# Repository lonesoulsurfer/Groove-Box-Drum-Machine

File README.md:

# Groove Box Drum Machine
An Arduino Nano based drum machine based on the awesome DrumKid build (https://github.com/mattybrad/drumkid) by Matt Bradshaw.  My version includes 3 X trigger outputs so you can sync with other synths.  I've also designed it so it will fit into any Eurorack and can be powered by either a standard 16 pin Eurorack power input or a 9V JST connector.

You can find a step by step guide on my Instructables page on how to build your own - https://www.instructables.com/Groove-Box-Arduino-Nano-Drum-Machine/

I have also posted a video on my YouTube page - https://youtu.be/VaNvsRpYE2A

The main goal with building this module is to create my own 'simple to build' modular synth. I wanted to keep everything as easy as possble with each module built with the following aims:

 - Can be powered by 9V (and 12V)
 - Easy to build with minimum components
 - Use Arduino to keep it simple (plus it helps to keep the components down and everything in tune)
 - Can fit into any modular synth Eurorck (include the ability to power the module via normal module power sources)
 - Has to sound great!
- Lastly, it should be portable and be powered from a 9V battery

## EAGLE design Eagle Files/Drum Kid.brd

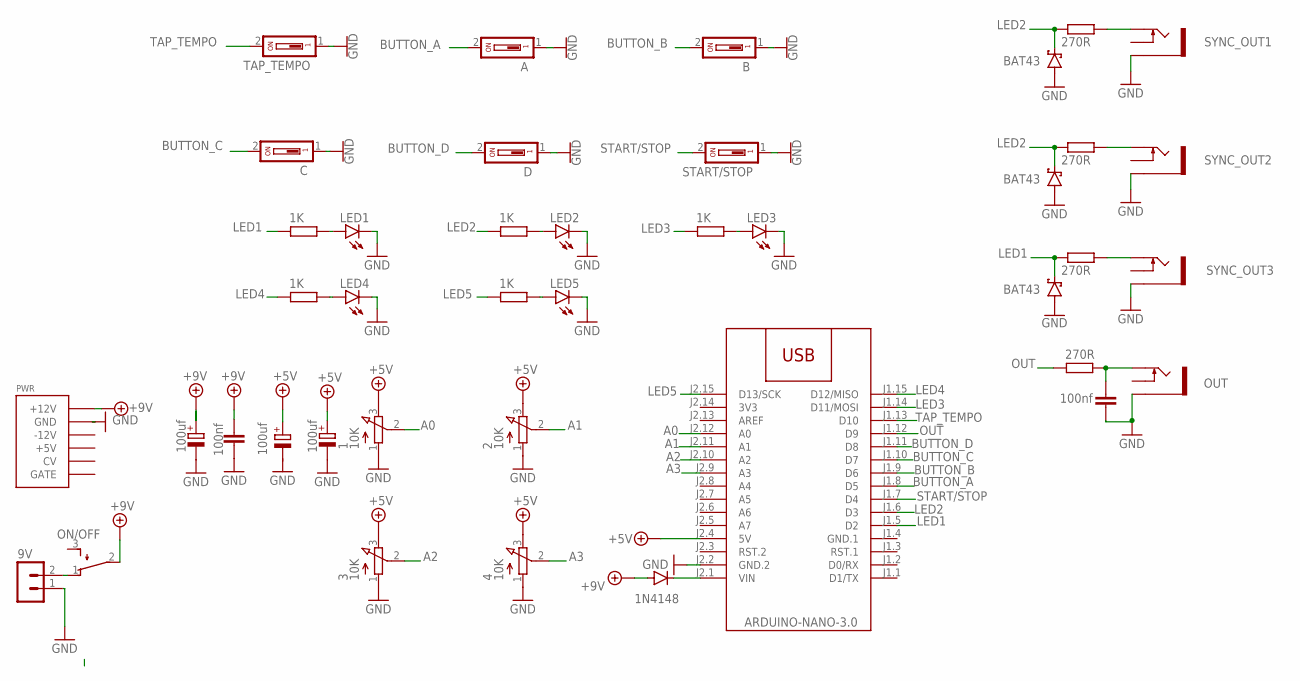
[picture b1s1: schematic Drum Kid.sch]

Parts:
1, 2, 3, 4: 10K; EVUF
9V: B2B-PH-K-S
A: DS01; DS-01
B: DS01; DS-01
C: DS01; DS-01
C1, C4: 100nf; C050-024X044
C2, C3: 100uf; E2-5
C5: 100uf; E2,5-6E
D: DS01; DS-01
D1, D3, D4: BAT43; DO35-10
D2: 1N4148; DO35-7
LED1, LED2, LED3, LED4, LED5: LED3MM
M1: ARDUINO-NANO-3.0
ON/OFF: TL32PO; TL3XPO
OUT: THONKICONNNEW; WQP-PJ301M-12_JACK
PWR: POWER; POWER_16
R1, R2, R3, R4, R5: 1K; 0207/10
R6, R7, R8, R9: 270R; 0207/10
START/STOP: DS01; DS-01
SYNC_OUT1, SYNC_OUT2, SYNC_OUT3: THONKICONNNEW; WQP-PJ301M-12_JACK
TAP_TEMPO: DS01; DS-01

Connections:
3V3: M1.J2.14 (3V3)
+5V: 1.3 (E), 2.3 (E), 3.3 (E), 4.3 (E), C2.+, C5.+, M1.J2.4 (5V)
+9V: C1.1, C3.+, D2.A, ON/OFF.2, PWR.9 (+12V), PWR.10 (+12V)
A0: 1.2 (S), M1.J2.12 (A0)
A1: 2.2 (S), M1.J2.11 (A1)
A2: 3.2 (S), M1.J2.10 (A2)
A3: 4.2 (S), M1.J2.9 (A3)
BUTTON_A: A.2, M1.J1.8 (D5)
BUTTON_B: B.2, M1.J1.9 (D6)
BUTTON_C: C.2, M1.J1.10 (D7)
BUTTON_D: D.2, M1.J1.11 (D8)
GND: 1.1 (A), 2.1 (A), 3.1 (A), 4.1 (A), 9V.1, A.1, B.1, C.1, C1.2, C2.-, C3.-, C4.2, D.1, D1.A, D3.A, D4.A, LED1.K (C), LED2.K (C), LED3.K (C), LED4.K (C), LED5.K (C), M1.J2.2 (GND.2), OUT.P$3_SLEEVE (SLEEVE), PWR.3 (GND), PWR.4 (GND), PWR.5 (GND), PWR.6 (GND), PWR.7 (GND), PWR.8 (GND), START/STOP.1, SYNC_OUT1.P$3_SLEEVE (SLEEVE), SYNC_OUT2.P$3_SLEEVE (SLEEVE), SYNC_OUT3.P$3_SLEEVE (SLEEVE), TAP_TEMPO.1
GND.1: M1.J1.4 (GND.1)
LED1: D3.C, M1.J1.5 (D2), R1.1, R6.1
LED2: D1.C, D4.C, M1.J1.6 (D3), R3.1, R7.1, R9.1
LED3: M1.J1.14 (D11/MOSI), R5.1
LED4: M1.J1.15 (D12/MISO), R2.1
LED5: M1.J2.15 (D13/SCK), R4.1
unnamed: 9V.2, ON/OFF.1 (O)
unnamed: LED1.A, R1.2
unnamed: C4.1, OUT.P$1_TIP (TIP), R8.2
unnamed: LED4.A, R2.2
unnamed: LED5.A, R4.2
unnamed: LED2.A, R3.2
unnamed: LED3.A, R5.2
unnamed: R7.2, SYNC_OUT1.P$1_TIP (TIP)
unnamed: R6.2, SYNC_OUT3.P$1_TIP (TIP)
unnamed: R9.2, SYNC_OUT2.P$1_TIP (TIP)
unnamed: D2.C, M1.J2.1 (VIN)
OUT: M1.J1.12 (D9), R8.1
START/STOP: M1.J1.7 (D4), START/STOP.2
TAP_TEMPO: M1.J1.13 (D10), TAP_TEMPO.2

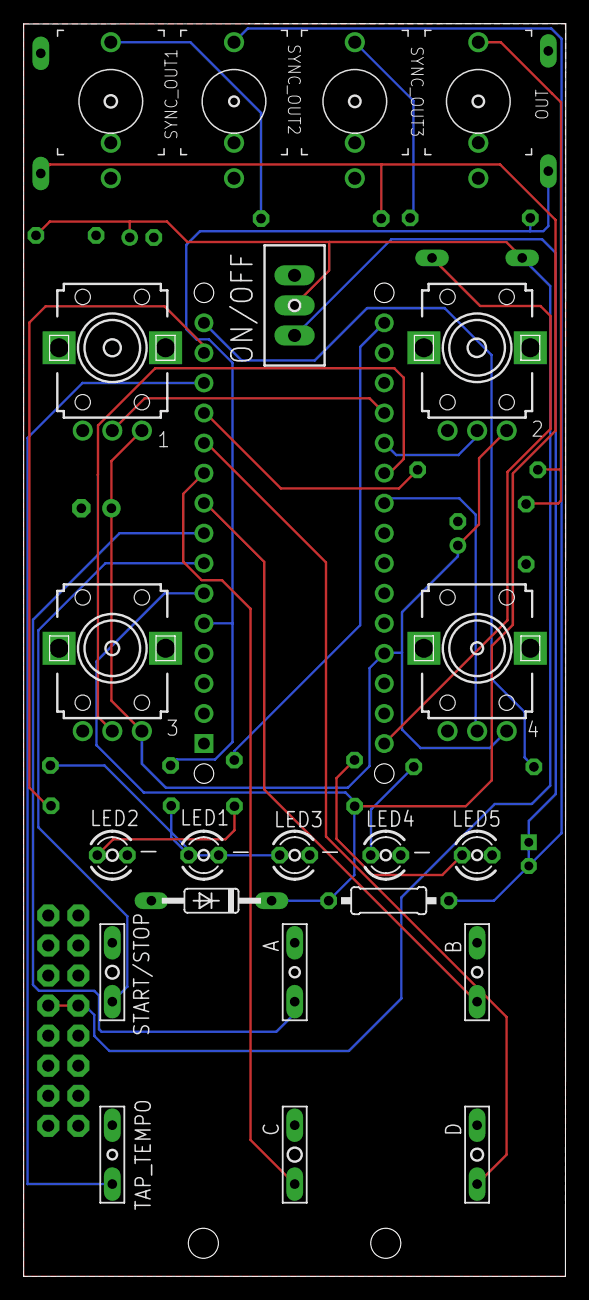
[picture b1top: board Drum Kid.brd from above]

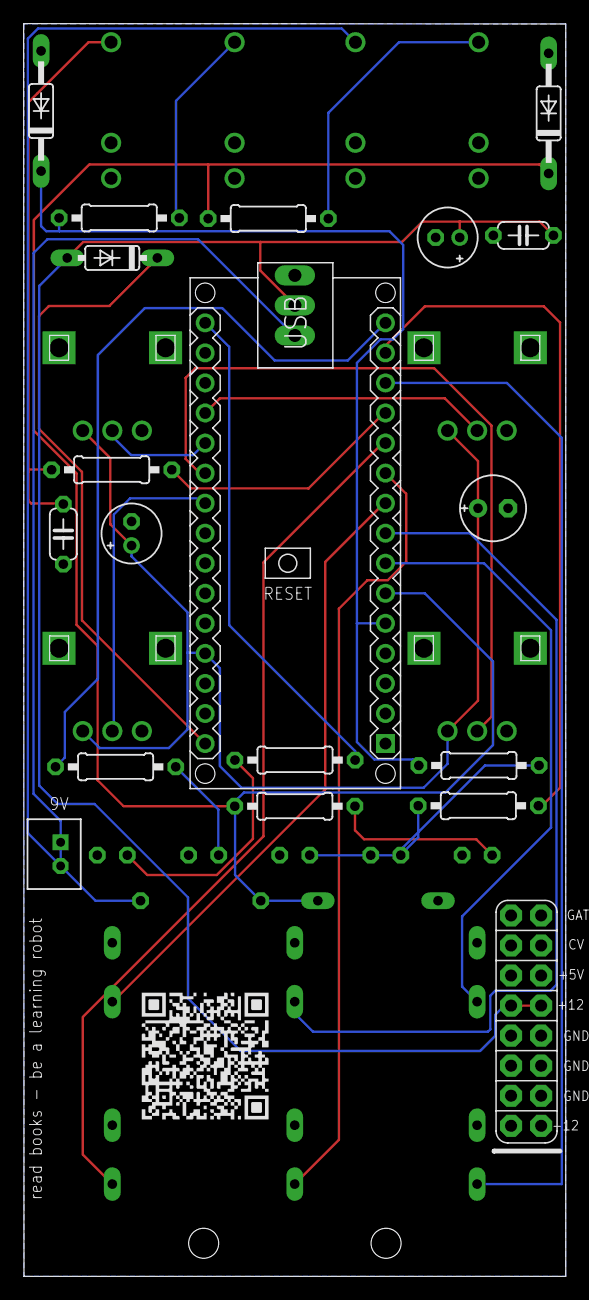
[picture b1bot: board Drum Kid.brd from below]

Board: 2 copper layers, 45.8 x 105.9 mm, 41 parts (19 on the bottom side), 30 nets.

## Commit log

2024-12-01 Drum Machine
2024-12-01 added Inkscape and kicad files
2024-12-01 Added Arduino Sketch
2024-12-02 Docs
2024-12-03 file
2024-12-03 Files

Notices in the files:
parts and their libraries:
diy-modules: Released under the Creative Commons Attribution 4.0 International License: http://creativecommons.org/licenses/by/4.0
SparkFun-PowerSymbols: Licensing: Creative Commons ShareAlike 4.0 International - https://creativecommons.org/licenses/by-sa/4.0
